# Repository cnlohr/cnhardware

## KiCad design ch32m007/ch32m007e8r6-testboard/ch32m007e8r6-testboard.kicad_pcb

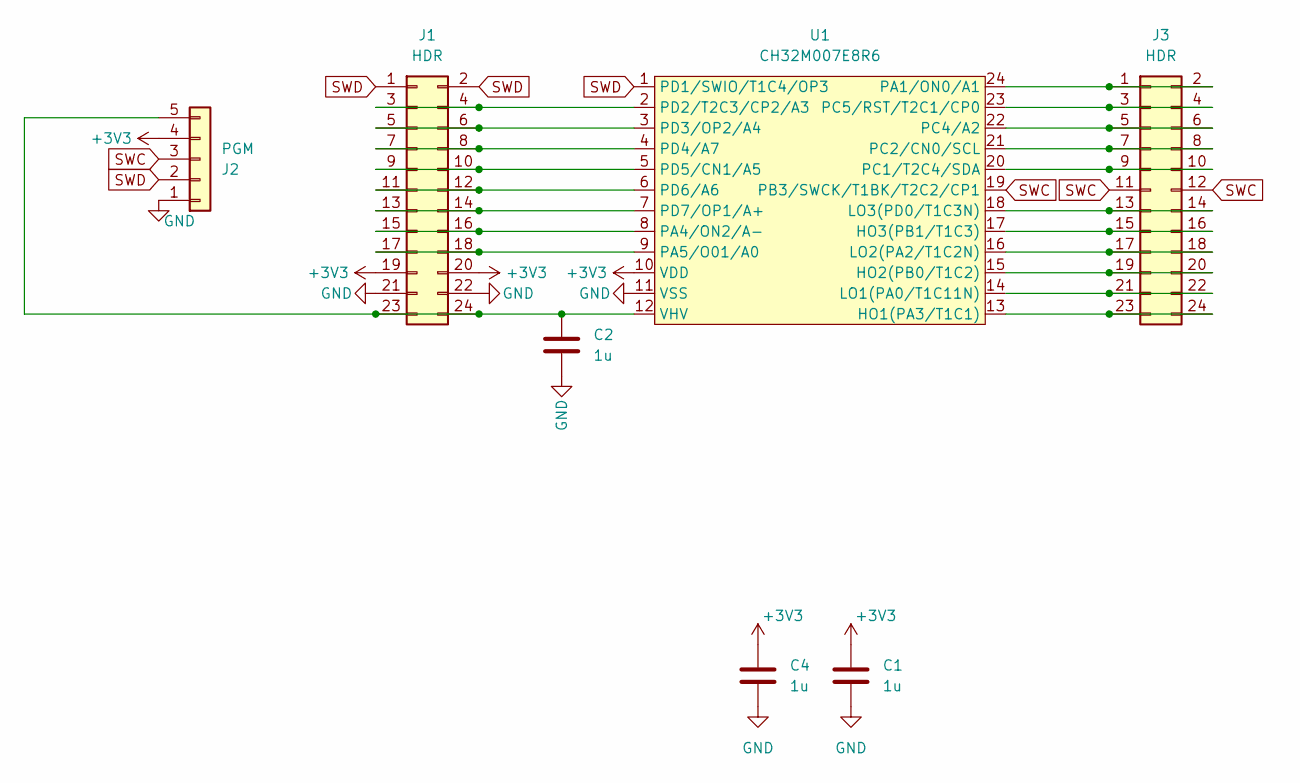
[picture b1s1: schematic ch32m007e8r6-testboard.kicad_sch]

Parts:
C1, C2, C4: 1u; C_0402_1005Metric; LCSC C52923
J1, J3: HDR; PinHeader_2x12_P2.54mm_Vertical; LCSC C492429
J2: PGM; PinHeader_1x05_P2.54mm_Vertical; LCSC C492404
U1: CH32M007E8R6; QSOP-24_3.9x8.7mm_P0.635mm

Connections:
+3V3: C1.1, C4.1, J1.19, J1.20, J2.4, U1.10 (VDD)
GND: C1.2, C2.2, C4.2, J1.21, J1.22, J2.1, U1.11 (VSS)
unnamed: J1.3, J1.4, U1.2 (PD2/T2C3/CP2/A3)
unnamed: J1.5, J1.6, U1.3 (PD3/OP2/A4)
unnamed: J1.7, J1.8, U1.4 (PD4/A7)
unnamed: J1.9, J1.10, U1.5 (PD5/CN1/A5)
unnamed: J1.11, J1.12, U1.6 (PD6/A6)
unnamed: J1.13, J1.14, U1.7 (PD7/OP1/A+)
unnamed: J1.15, J1.16, U1.8 (PA4/ON2/A-)
unnamed: J1.17, J1.18, U1.9 (PA5/O01/A0)
unnamed: C2.1, J1.23, J1.24, J2.5, U1.12 (VHV)
unnamed: J3.1, J3.2, U1.24 (PA1/ON0/A1)
unnamed: J3.3, J3.4, U1.23 (PC5/RST/T2C1/CP0)
unnamed: J3.5, J3.6, U1.22 (PC4/A2)
unnamed: J3.7, J3.8, U1.21 (PC2/CN0/SCL)
unnamed: J3.9, J3.10, U1.20 (PC1/T2C4/SDA)
unnamed: J3.13, J3.14, U1.18 (LO3(PD0/T1C3N))
unnamed: J3.15, J3.16, U1.17 (HO3(PB1/T1C3))
unnamed: J3.17, J3.18, U1.16 (LO2(PA2/T1C2N))
unnamed: J3.19, J3.20, U1.15 (HO2(PB0/T1C2))
unnamed: J3.21, J3.22, U1.14 (LO1(PA0/T1C11N))
unnamed: J3.23, J3.24, U1.13 (HO1(PA3/T1C1))
SWC: J2.3, J3.11, J3.12, U1.19 (PB3/SWCK/T1BK/T2C2/CP1)
SWD: J1.1, J1.2, J2.2, U1.1 (PD1/SWIO/T1C4/OP3)

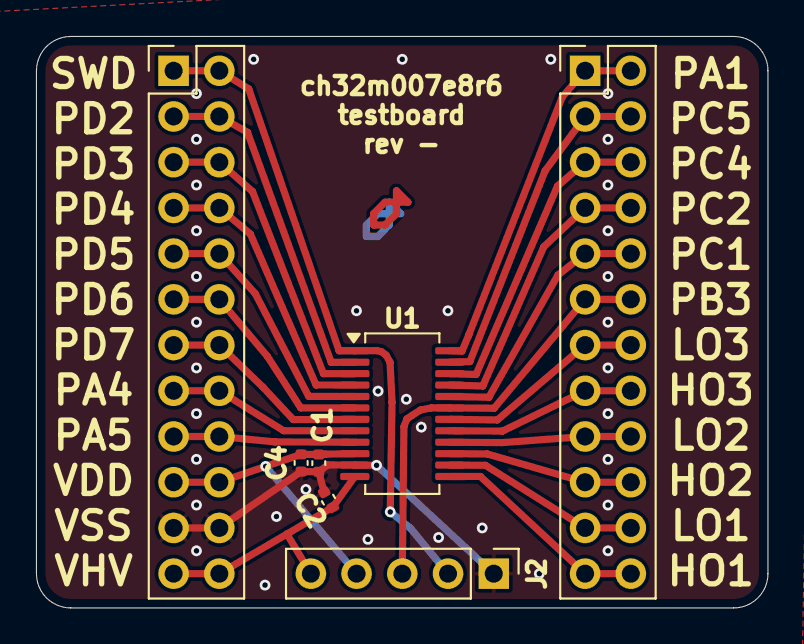
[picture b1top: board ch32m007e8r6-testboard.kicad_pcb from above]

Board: 2 copper layers, 40.6 x 31.8 mm, 7 parts (0 on the bottom side), 24 nets.

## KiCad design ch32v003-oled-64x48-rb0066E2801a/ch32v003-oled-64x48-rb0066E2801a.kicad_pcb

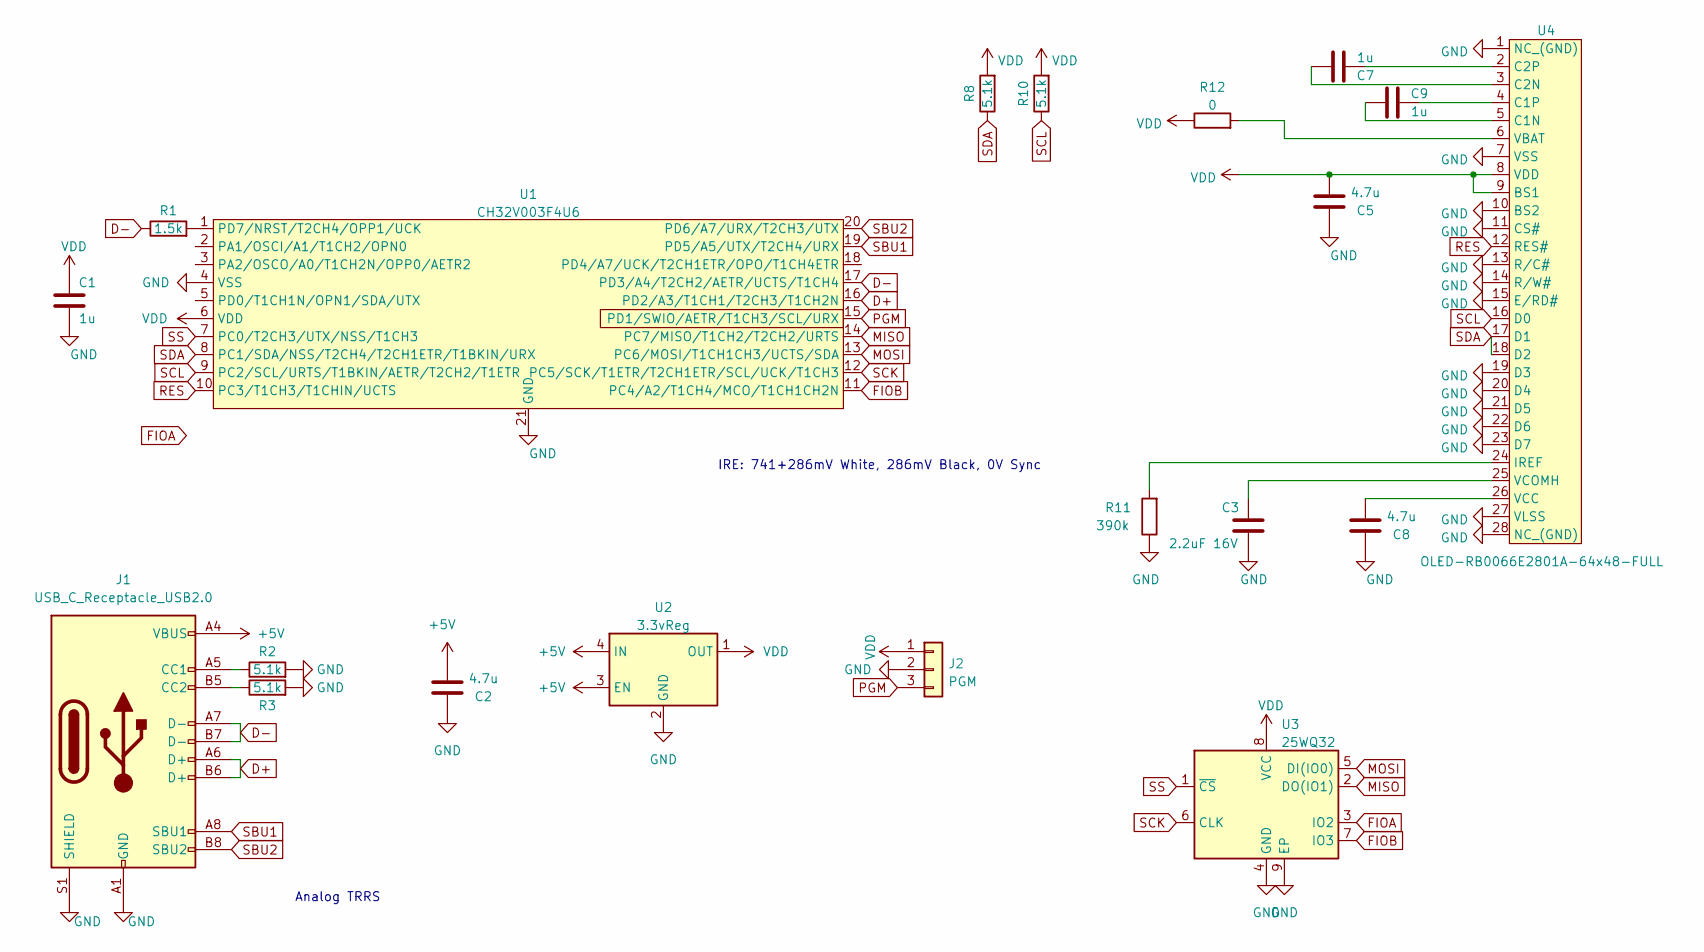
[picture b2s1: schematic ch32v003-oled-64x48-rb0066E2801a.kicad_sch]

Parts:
C1, C7, C9: 1u; R_0402_1005Metric; LCSC C52923
C2, C5, C8: 4.7u; R_0402_1005Metric; LCSC C368809
C3: 2.2uF 16V; R_0402_1005Metric; LCSC C668369
J1: USB_C_Receptacle_USB2.0; USB_C_Receptacle_HRO_TYPE-C-31-M-12; LCSC C2765186
J2: PGM; PinHeader_1x03_P2.54mm_Vertical
R1: 1.5k; R_0402_1005Metric; LCSC C25867
R2, R3, R8, R10: 5.1k; R_0402_1005Metric; LCSC C25905
R11: 390k; R_0402_1005Metric; LCSC C163467
R12: 0; R_0402_1005Metric; LCSC C17168
U1: CH32V003F4U6; QFN-20-1EP_3x3mm_P0.4mm_EP1.65x1.65mm; LCSC C5299908
U2: 3.3vReg; xdfn-reg; LCSC C379350
U3: 25WQ32; LCSC NP_C5258281
U4: OLED-RB0066E2801A-64x48-FULL

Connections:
+5V: C2.2, J1.A4 (VBUS), J1.A9 (VBUS), J1.B4 (VBUS), J1.B9 (VBUS), U2.3 (EN), U2.4 (IN)
D+: J1.A6 (D+), J1.B6 (D+), U1.16 (PD2/A3/T1CH1/T2CH3/T1CH2N)
D-: J1.A7 (D-), J1.B7 (D-), R1.1, U1.17 (PD3/A4/T2CH2/AETR/UCTS/T1CH4)
FIOB: U1.11 (PC4/A2/T1CH4/MCO/T1CH1CH2N), U3.7 (IO3)
GND: C1.1, C2.1, C3.1, C5.1, C8.1, J1.A1 (GND), J1.A12 (GND), J1.B1 (GND), J1.B12 (GND), J1.S1 (SHIELD), J2.2, R2.2, R3.2, R11.1, U1.4 (VSS), U1.21 (GND), U2.2 (GND), U2.5 (GND), U3.4 (GND), U3.9 (EP), U4.1 (NC_(GND)), U4.7 (VSS), U4.10 (BS2), U4.11 (CS#), U4.13 (R/C#), U4.14 (R/W#), U4.15 (E/RD#), U4.19 (D3), U4.20 (D4), U4.21 (D5), U4.22 (D6), U4.23 (D7), U4.27 (VLSS), U4.28 (NC_(GND))
MISO: U1.14 (PC7/MISO/T1CH2/T2CH2/URTS), U3.2 (DO(IO1))
MOSI: U1.13 (PC6/MOSI/T1CH1CH3/UCTS/SDA), U3.5 (DI(IO0))
unnamed: C3.2, U4.25 (VCOMH)
unnamed: C7.1, U4.3 (C2N)
unnamed: C7.2, U4.2 (C2P)
unnamed: C8.2, U4.26 (VCC)
unnamed: C9.1, U4.5 (C1N)
unnamed: C9.2, U4.4 (C1P)
unnamed: J1.A5 (CC1), R2.1
unnamed: J1.B5 (CC2), R3.1
unnamed: R1.2, U1.1 (PD7/NRST/T2CH4/OPP1/UCK)
unnamed: R11.2, U4.24 (IREF)
unnamed: R12.2, U4.6 (VBAT)
PGM: J2.3, U1.15 (PD1/SWIO/AETR/T1CH3/SCL/URX)
RES: U1.10 (PC3/T1CH3/T1CHIN/UCTS), U4.12 (RES#)
SBU1: J1.A8 (SBU1), U1.19 (PD5/A5/UTX/T2CH4/URX)
SBU2: J1.B8 (SBU2), U1.20 (PD6/A7/URX/T2CH3/UTX)
SCK: U1.12 (PC5/SCK/T1ETR/T2CH1ETR/SCL/UCK/T1CH3), U3.6 (CLK)
SCL: R10.1, U1.9 (PC2/SCL/URTS/T1BKIN/AETR/T2CH2/T1ETR), U4.16 (D0)
SDA: R8.1, U1.8 (PC1/SDA/NSS/T2CH4/T2CH1ETR/T1BKIN/URX), U4.17 (D1), U4.18 (D2)
SS: U1.7 (PC0/T2CH3/UTX/NSS/T1CH3), U3.1 (~CS)
VDD: C1.2, C5.2, J2.1, R8.2, R10.2, R12.1, U1.6 (VDD), U2.1 (OUT), U3.8 (VCC), U4.8 (VDD), U4.9 (BS1)

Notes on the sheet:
IRE: 741+286mV White, 286mV Black, 0V Sync
Analog TRRS

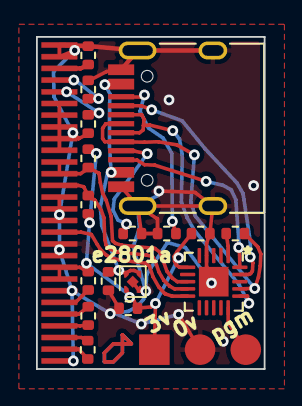
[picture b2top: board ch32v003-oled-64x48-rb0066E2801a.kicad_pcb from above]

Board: 2 copper layers, 12.7 x 18.5 mm, 19 parts (0 on the bottom side), 22 nets.

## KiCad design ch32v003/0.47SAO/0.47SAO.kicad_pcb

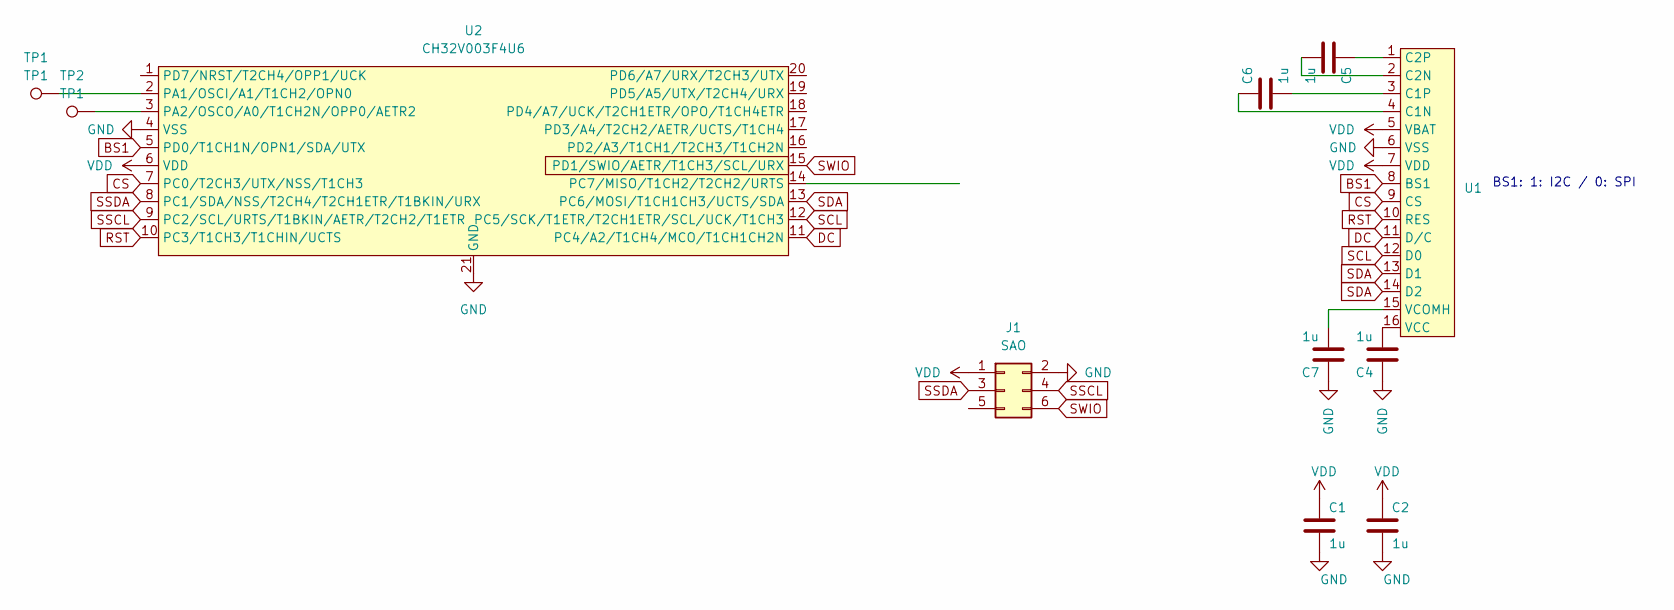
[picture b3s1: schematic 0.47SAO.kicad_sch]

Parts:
C1, C2, C4, C5, C6, C7: 1u; R_0402_1005Metric; LCSC C52923
J1: SAO; PinHeader_2x03_P2.54mm_Vertical_SMD
TP1, TP2: TP1; TestPoint_Pad_D2.5mm
U1: P0.65mm_16_pin_OLED_FLEX_CONTACT
U2: CH32V003F4U6; QFN-20-1EP_3x3mm_P0.4mm_EP1.65x1.65mm; LCSC C5299908

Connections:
BS1: U1.8 (BS1), U2.5 (PD0/T1CH1N/OPN1/SDA/UTX)
CS: U1.9 (CS), U2.7 (PC0/T2CH3/UTX/NSS/T1CH3)
DC: U1.11 (D/C), U2.11 (PC4/A2/T1CH4/MCO/T1CH1CH2N)
GND: C1.1, C2.1, C4.2, C7.2, J1.2, U1.6 (VSS), U2.4 (VSS), U2.21 (GND)
unnamed: C6.2, U1.4 (C1N)
unnamed: C6.1, U1.3 (C1P)
unnamed: C5.1, U1.2 (C2N)
unnamed: C5.2, U1.1 (C2P)
unnamed: C4.1, U1.16 (VCC)
unnamed: C7.1, U1.15 (VCOMH)
unnamed: TP1.1, U2.2 (PA1/OSCI/A1/T1CH2/OPN0)
unnamed: TP2.1, U2.3 (PA2/OSCO/A0/T1CH2N/OPP0/AETR2)
RST: U1.10 (RES), U2.10 (PC3/T1CH3/T1CHIN/UCTS)
SCL: U1.12 (D0), U2.12 (PC5/SCK/T1ETR/T2CH1ETR/SCL/UCK/T1CH3)
SDA: U1.13 (D1), U1.14 (D2), U2.13 (PC6/MOSI/T1CH1CH3/UCTS/SDA)
SSCL: J1.4, U2.9 (PC2/SCL/URTS/T1BKIN/AETR/T2CH2/T1ETR)
SSDA: J1.3, U2.8 (PC1/SDA/NSS/T2CH4/T2CH1ETR/T1BKIN/URX)
SWIO: J1.6, U2.15 (PD1/SWIO/AETR/T1CH3/SCL/URX)
VDD: C1.2, C2.2, J1.1, U1.5 (VBAT), U1.7 (VDD), U2.6 (VDD)

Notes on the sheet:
BS1: 1: I2C / 0: SPI

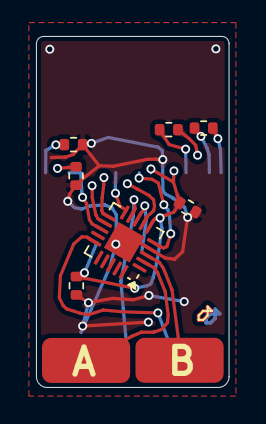
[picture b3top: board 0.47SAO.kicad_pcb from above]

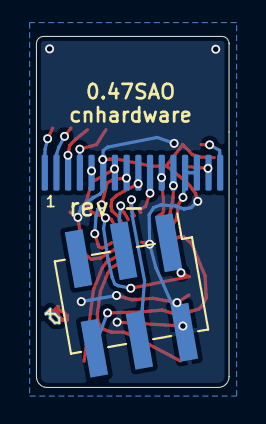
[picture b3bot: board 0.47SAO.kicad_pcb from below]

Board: 2 copper layers, 10.7 x 19.5 mm, 11 parts (2 on the bottom side), 19 nets.

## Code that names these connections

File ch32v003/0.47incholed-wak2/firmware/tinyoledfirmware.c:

#include "ch32v003fun.h"
#include <stdio.h>
#include <string.h>
#include "rv003usb.h"



// what type of OLED - uncomment just one
//#define SSD1306_64X32
//#define SSD1306_128X32
//#define SSD1306_128X64

#define SSD1306_W 72
#define SSD1306_H 40
#define SSD1306_FULLUSE
#define SSD1306_OFFSET 28

// control pins
#define SSD1306_RST_PIN PC3
#define SSD1306_CS_PIN PC2
#define SSD1306_DC_PIN PC4
#define SSD1306_MOSI_PIN PC6
#define SSD1306_SCK_PIN  PC5

#define SSD1306_BAUD_RATE_PRESCALER SPI_BaudRatePrescaler_2


#include "ssd1306_spi.h"
#include "ssd1306.h"


// Allow reading and writing to the scratchpad via HID control messages.
uint8_t scratch[368];
volatile int start_leds = 0;
static int frame;


int main()
{
	SystemInit();
	funPinMode( PD3, GPIO_CFGLR_OUT_50Mhz_PP );
	funPinMode( PD4, GPIO_CFGLR_OUT_50Mhz_PP );
	funDigitalWrite( PD3, FUN_LOW );
	funDigitalWrite( PD4, FUN_LOW );
	Delay_Ms(1000); // Ensures USB re-enumeration after bootloader or reset; Spec demand >2.5µs ( TDDIS )
	usb_setup();

	funGpioInitAll();
	funPinMode( PA1, GPIO_CFGLR_OUT_50Mhz_PP );
	funPinMode( PA2, GPIO_CFGLR_OUT_50Mhz_PP );
	funDigitalWrite( PA1, FUN_LOW );
	funDigitalWrite( PA2, FUN_LOW );

	ssd1306_rst();
	if(ssd1306_spi_init())
	{
		printf( "Could not connect to OLED\n" );
	}
	ssd1306_init();

	ssd1306_cmd( SSD1306_SETMULTIPLEX );
	ssd1306_cmd( 39 );
	ssd1306_cmd( SSD1306_SETDISPLAYOFFSET );
	ssd1306_cmd( 0 );

	ssd1306_cmd( SSD1306_SETPRECHARGE ); ssd1306_cmd( 0xf1 );
	ssd1306_cmd( SSD1306_SETCONTRAST ); ssd1306_cmd( 0xf1 );
	ssd1306_cmd( SSD1306_SETVCOMDETECT ); ssd1306_cmd( 0x40 );
	ssd1306_cmd( 0xad ); ssd1306_cmd( 0x90 ); // Set Charge pump (set to 0x90 for extra bright)

	int i;
	/* fill with random */
	for(i=0;i<sizeof(ssd1306_buffer);i++)
	{
		ssd1306_buffer[i] = (i&1)?0xaa:0x55;//(i == (frame&0x1ff) ) ? 0x00: 0xff;
	}
	frame++;

	ssd1306_cmd(SSD1306_COLUMNADDR);
	ssd1306_cmd(28);   // Column start address (0 = reset)
	ssd1306_cmd(28+71); // Column end address (127 = reset)
	
	ssd1306_cmd(SSD1306_PAGEADDR);
	ssd1306_cmd(0); // Page start address (0 = reset)
	ssd1306_cmd(5); // Page end address

	for(i=0;i<sizeof(ssd1306_buffer);i+=SSD1306_PSZ)
	{
		ssd1306_data(&ssd1306_buffer[i], SSD1306_PSZ);
	}

	Delay_Ms(2);

	while(1)
	{
		//printf( "%lu %lu %lu %08lx\n", rv003usb_internal_data.delta_se0_cyccount, rv003usb_internal_data.last_se0_cyccount, rv003usb_internal_data.se0_windup, RCC->CTLR );
#if RV003USB_EVENT_DEBUGGING
		uint32_t * ue = GetUEvent();
		if( ue )
		{
			printf( "%lu %lx %lx %lx\n", ue[0], ue[1], ue[2], ue[3] );
		}
#endif
		if( start_leds )
		{
			//WS2812BSimpleSend( GPIOC, 6, scratch + 3, 6*3 );
			uint8_t * sp = scratch + 4;
	ssd1306_cmd( SSD1306_SETPRECHARGE ); ssd1306_cmd( scratch[1] );
	ssd1306_cmd( SSD1306_SETCONTRAST ); ssd1306_cmd( scratch[2] );
	ssd1306_cmd( SSD1306_SETVCOMDETECT ); ssd1306_cmd( scratch[3] );

		//	printf( "%d\n", start_leds );

			ssd1306_cmd(SSD1306_COLUMNADDR);
			ssd1306_cmd(28);   // Column start address (0 = reset)
			ssd1306_cmd(28+71); // Column end address (127 = reset)
			
			ssd1306_cmd(SSD1306_PAGEADDR);
			ssd1306_cmd(0); // Page start address (0 = reset)
			ssd1306_cmd(5); // Page end address

			ssd1306_data( sp, 180 );
			ssd1306_data( sp+180, 180 );

			start_leds = 0;
			frame++;
		}
	}
}

void usb_handle_user_in_request( struct usb_endpoint * e, uint8_t * scratchpad, int endp, uint32_t sendtok, struct rv003usb_internal * ist )
{
	// Make sure we only deal with control messages.  Like get/set feature reports.
	if( endp )
	{
		usb_send_empty( sendtok );
	}
}

void usb_handle_user_data( struct usb_endpoint * e, int current_endpoint, uint8_t * data, int len, struct rv003usb_internal * ist )
{
	//LogUEvent( SysTick->CNT, current_endpoint, e->count, 0xaaaaaaaa );
	int offset = e->count<<3;
	int torx = e->max_len - offset;
	if( torx > len ) torx = len;
	if( torx > 0 )
	{
		memcpy( scratch + offset, data, torx );
		e->count++;
		if( ( e->count << 3 ) >= e->max_len )
		{
			start_leds = e->max_len;
		}
	}
}

void usb_handle_hid_get_report_start( struct usb_endpoint * e, int reqLen, uint32_t lValueLSBIndexMSB )
{
	if( reqLen > sizeof( scratch ) ) reqLen = sizeof( scratch );

	// You can check the lValueLSBIndexMSB word to decide what you want to do here
	// But, whatever you point this at will be returned back to the host PC where
	// it calls hid_get_feature_report. 
	//
	// Please note, that on some systems, for this to work, your return length must
	// match the length defined in HID_REPORT_COUNT, in your HID report, in usb_config.h

	e->opaque = scratch;
	e->max_len = reqLen;
}

void usb_handle_hid_set_report_start( struct usb_endpoint * e, int reqLen, uint32_t lValueLSBIndexMSB )
{
	// Here is where you get an alert when the host PC calls hid_send_feature_report.
	//
	// You can handle the appropriate message here.  Please note that in this
	// example, the data is chunked into groups-of-8-bytes.
	//
	// Note that you may need to make this match HID_REPORT_COUNT, in your HID
	// report, in usb_config.h

	if( reqLen > sizeof( scratch ) ) reqLen = sizeof( scratch );
	e->max_len = reqLen;
}


void usb_handle_other_control_message( struct usb_endpoint * e, struct usb_urb * s, struct rv003usb_internal * ist )
{
	LogUEvent( SysTick->CNT, s->wRequestTypeLSBRequestMSB, s->lValueLSBIndexMSB, s->wLength );
}

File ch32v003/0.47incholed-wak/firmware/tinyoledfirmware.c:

#include "ch32v003fun.h"
#include <stdio.h>
#include <string.h>
#include "rv003usb.h"



// what type of OLED - uncomment just one
//#define SSD1306_64X32
//#define SSD1306_128X32
//#define SSD1306_128X64

#define SSD1306_W 72
#define SSD1306_H 40
#define SSD1306_FULLUSE
#define SSD1306_OFFSET 28

// control pins
#define SSD1306_RST_PIN PD6
#define SSD1306_CS_PIN PD7
#define SSD1306_DC_PIN PD2
#define SSD1306_MOSI_PIN PC6
#define SSD1306_SCK_PIN  PC5

#define SSD1306_BAUD_RATE_PRESCALER SPI_BaudRatePrescaler_2


#include "ssd1306_spi.h"
#include "ssd1306.h"


// Allow reading and writing to the scratchpad via HID control messages.
uint8_t scratch[368];
volatile int start_leds = 0;
static int frame;


int main()
{
	SystemInit();
	funPinMode( PD3, GPIO_CFGLR_OUT_50Mhz_PP );
	funPinMode( PD4, GPIO_CFGLR_OUT_50Mhz_PP );
	funDigitalWrite( PD3, FUN_LOW );
	funDigitalWrite( PD4, FUN_LOW );
	Delay_Ms(1000); // Ensures USB re-enumeration after bootloader or reset; Spec demand >2.5µs ( TDDIS )
	usb_setup();

	funGpioInitAll();
	funPinMode( PA1, GPIO_CFGLR_OUT_50Mhz_PP );
	funPinMode( PA2, GPIO_CFGLR_OUT_50Mhz_PP );
	funDigitalWrite( PA1, FUN_LOW );
	funDigitalWrite( PA2, FUN_LOW );

	ssd1306_rst();
	if(ssd1306_spi_init())
	{
		printf( "Could not connect to OLED\n" );
	}
	ssd1306_init();

	ssd1306_cmd( SSD1306_SETMULTIPLEX );
	ssd1306_cmd( 39 );
	ssd1306_cmd( SSD1306_SETDISPLAYOFFSET );
	ssd1306_cmd( 0 );

	ssd1306_cmd( SSD1306_SETPRECHARGE ); ssd1306_cmd( 0xf1 );
	ssd1306_cmd( SSD1306_SETCONTRAST ); ssd1306_cmd( 0xf1 );
	ssd1306_cmd( SSD1306_SETVCOMDETECT ); ssd1306_cmd( 0x40 );
	ssd1306_cmd( 0xad ); ssd1306_cmd( 0x90 ); // Set Charge pump (set to 0x90 for extra bright)

	int i;
	/* fill with random */
	for(i=0;i<sizeof(ssd1306_buffer);i++)
	{
		ssd1306_buffer[i] = (i&1)?0xaa:0x55;//(i == (frame&0x1ff) ) ? 0x00: 0xff;
	}
	frame++;

	ssd1306_cmd(SSD1306_COLUMNADDR);
	ssd1306_cmd(28);   // Column start address (0 = reset)
	ssd1306_cmd(28+71); // Column end address (127 = reset)
	
	ssd1306_cmd(SSD1306_PAGEADDR);
	ssd1306_cmd(0); // Page start address (0 = reset)
	ssd1306_cmd(5); // Page end address

	for(i=0;i<sizeof(ssd1306_buffer);i+=SSD1306_PSZ)
	{
		ssd1306_data(&ssd1306_buffer[i], SSD1306_PSZ);
	}

	Delay_Ms(2);

	while(1)
	{
		//printf( "%lu %lu %lu %08lx\n", rv003usb_internal_data.delta_se0_cyccount, rv003usb_internal_data.last_se0_cyccount, rv003usb_internal_data.se0_windup, RCC->CTLR );
#if RV003USB_EVENT_DEBUGGING
		uint32_t * ue = GetUEvent();
		if( ue )
		{
			printf( "%lu %lx %lx %lx\n", ue[0], ue[1], ue[2], ue[3] );
		}
#endif
		if( start_leds )
		{
			//WS2812BSimpleSend( GPIOC, 6, scratch + 3, 6*3 );
			uint8_t * sp = scratch + 4;
	ssd1306_cmd( SSD1306_SETPRECHARGE ); ssd1306_cmd( scratch[1] );
	ssd1306_cmd( SSD1306_SETCONTRAST ); ssd1306_cmd( scratch[2] );
	ssd1306_cmd( SSD1306_SETVCOMDETECT ); ssd1306_cmd( scratch[3] );

		//	printf( "%d\n", start_leds );

			ssd1306_cmd(SSD1306_COLUMNADDR);
			ssd1306_cmd(28);   // Column start address (0 = reset)
			ssd1306_cmd(28+71); // Column end address (127 = reset)
			
			ssd1306_cmd(SSD1306_PAGEADDR);
			ssd1306_cmd(0); // Page start address (0 = reset)
			ssd1306_cmd(5); // Page end address

			ssd1306_data( sp, 180 );
			ssd1306_data( sp+180, 180 );

			start_leds = 0;
			frame++;
		}
	}
}

void usb_handle_user_in_request( struct usb_endpoint * e, uint8_t * scratchpad, int endp, uint32_t sendtok, struct rv003usb_internal * ist )
{
	// Make sure we only deal with control messages.  Like get/set feature reports.
	if( endp )
	{
		usb_send_empty( sendtok );
	}
}

void usb_handle_user_data( struct usb_endpoint * e, int current_endpoint, uint8_t * data, int len, struct rv003usb_internal * ist )
{
	//LogUEvent( SysTick->CNT, current_endpoint, e->count, 0xaaaaaaaa );
	int offset = e->count<<3;
	int torx = e->max_len - offset;
	if( torx > len ) torx = len;
	if( torx > 0 )
	{
		memcpy( scratch + offset, data, torx );
		e->count++;
		if( ( e->count << 3 ) >= e->max_len )
		{
			start_leds = e->max_len;
		}
	}
}

void usb_handle_hid_get_report_start( struct usb_endpoint * e, int reqLen, uint32_t lValueLSBIndexMSB )
{
	if( reqLen > sizeof( scratch ) ) reqLen = sizeof( scratch );

	// You can check the lValueLSBIndexMSB word to decide what you want to do here
	// But, whatever you point this at will be returned back to the host PC where
	// it calls hid_get_feature_report. 
	//
	// Please note, that on some systems, for this to work, your return length must
	// match the length defined in HID_REPORT_COUNT, in your HID report, in usb_config.h

	e->opaque = scratch;
	e->max_len = reqLen;
}

void usb_handle_hid_set_report_start( struct usb_endpoint * e, int reqLen, uint32_t lValueLSBIndexMSB )
{
	// Here is where you get an alert when the host PC calls hid_send_feature_report.
	//
	// You can handle the appropriate message here.  Please note that in this
	// example, the data is chunked into groups-of-8-bytes.
	//
	// Note that you may need to make this match HID_REPORT_COUNT, in your HID
	// report, in usb_config.h

	if( reqLen > sizeof( scratch ) ) reqLen = sizeof( scratch );
	e->max_len = reqLen;
}


void usb_handle_other_control_message( struct usb_endpoint * e, struct usb_urb * s, struct rv003usb_internal * ist )
{
	LogUEvent( SysTick->CNT, s->wRequestTypeLSBRequestMSB, s->lValueLSBIndexMSB, s->wLength );
}
